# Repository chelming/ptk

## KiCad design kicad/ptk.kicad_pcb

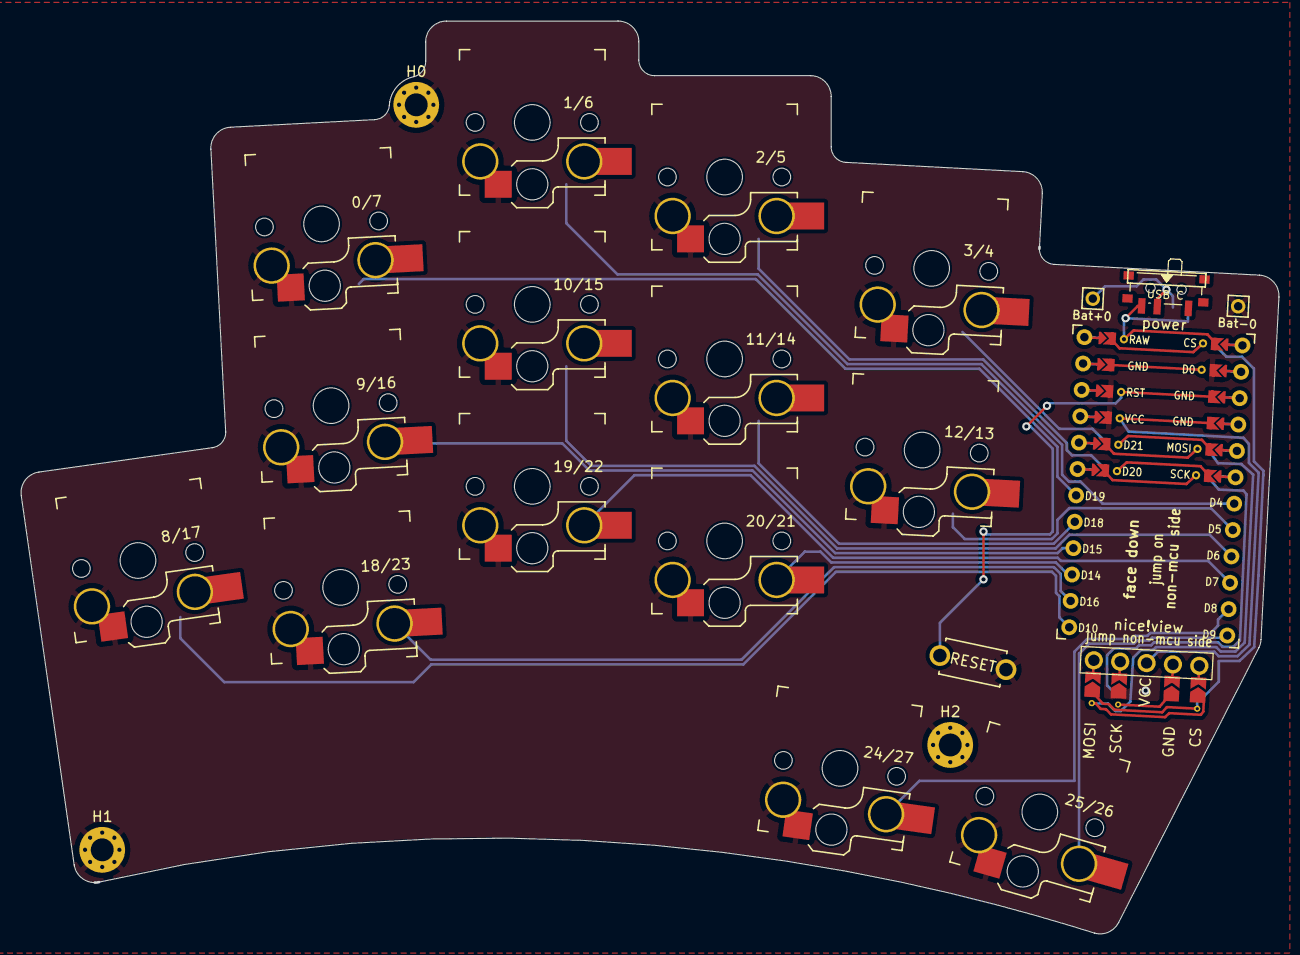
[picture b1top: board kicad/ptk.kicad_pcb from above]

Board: 2 copper layers, 121.0 x 87.8 mm, 23 parts (0 on the bottom side), 22 nets.

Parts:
0/7, 1/6, 2/5, 3/4, 8/17, 9/16, 10/15, 11/14, 12/13, 18/23, 19/22, 20/21, 24/27, 25/26: keyswitch; choc_v1_hotswap_reversible
Bat+0: MountingHole_Pad; 1pin_conn
Bat-0: MountingHole_Pad; 1pin_conn
H0, H1, H2: MountingHole_Pad; MountingHole_2.2mm_M2_Pad_Via
J0: nice!view; nice-view_reversible
MCU0: ProMicro-kbd; ProMicro_v3_nice_view_reversible
RSW0: SW_Push; ResetSW
SW_PWR0: SW_SPST; SW_SPDT_PCM12_REVERSIBLE

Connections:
+BATT: Bat+0.1, SW_PWR0.1 (A)
GND: 0/7.1, 1/6.1, 2/5.1, 3/4.1, 8/17.1, 9/16.1, 10/15.1, 11/14.1, 12/13.1, 18/23.1, 19/22.1, 20/21.1, 24/27.1, 25/26.1, Bat-0.1, H0.1, H1.1, H2.1, J0.4, MCU0.3 (GND), MCU0.4 (GND), MCU0.23 (GND), RSW0.1
VCC: J0.3, MCU0.21 (VCC)
cs: J0.5, MCU0.1 (TX)
mosi: J0.1, MCU0.5 (SDA)
raw: MCU0.24 (RAW), SW_PWR0.2 (B)
reset: MCU0.22 (RST), RSW0.2
s0: 0/7.2, MCU0.18 (F6)
s1: 1/6.2, MCU0.7 (D4)
s2: 2/5.2, MCU0.19 (F5)
s3: 3/4.2, MCU0.20 (F4)
s8: 8/17.2, MCU0.13 (B6)
s9: 9/16.2, MCU0.16 (B1)
s10: 10/15.2, MCU0.9 (D7)
s11: 11/14.2, MCU0.17 (F7)
s12: 12/13.2, MCU0.8 (C6)
s18: 18/23.2, MCU0.14 (B2)
s19: 19/22.2, MCU0.10 (E6)
s20: 20/21.2, MCU0.15 (B3)
s24: 24/27.2, MCU0.11 (B4)
s25: 25/26.2, MCU0.12 (B5)
sck: J0.2, MCU0.6 (SCL)

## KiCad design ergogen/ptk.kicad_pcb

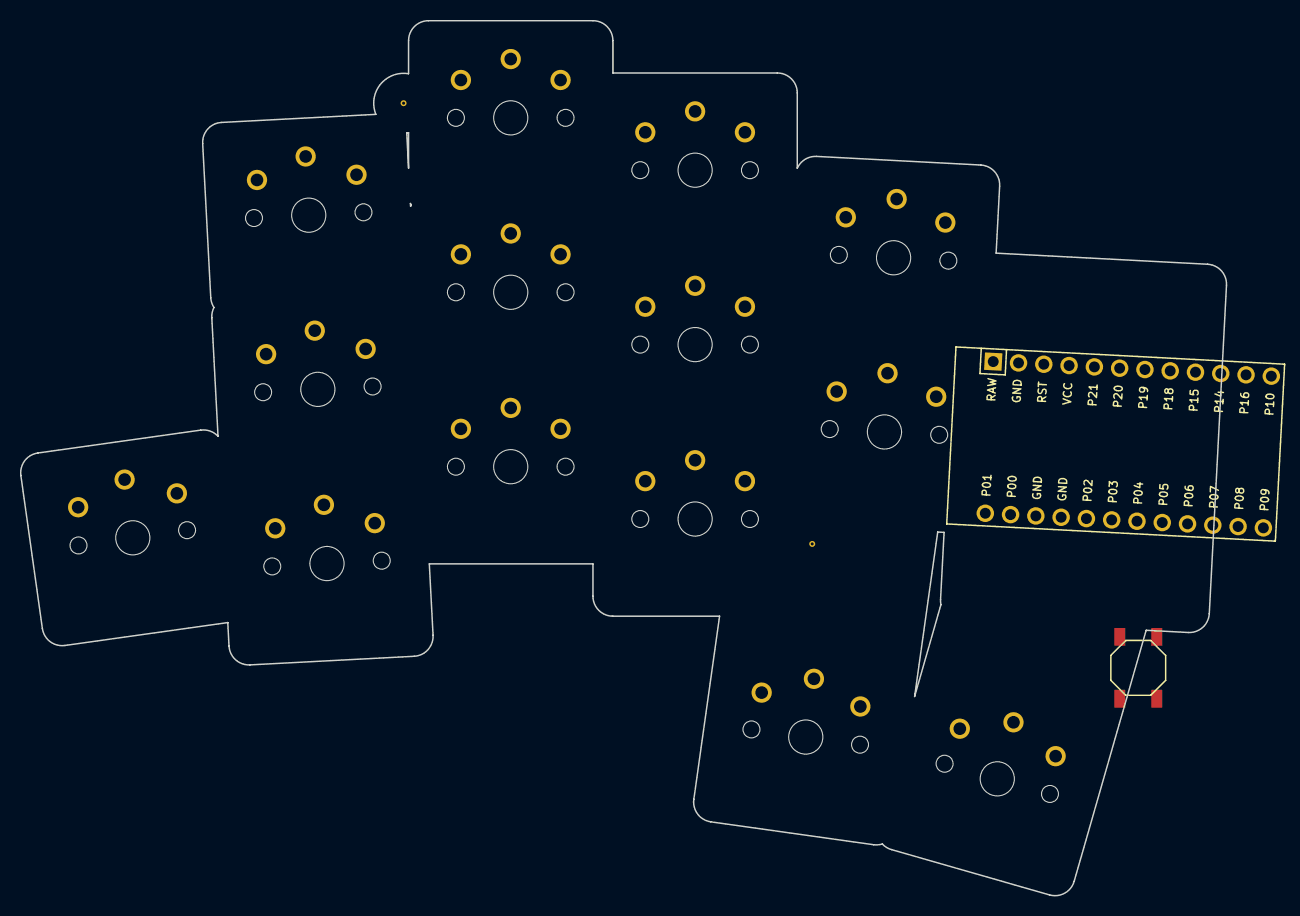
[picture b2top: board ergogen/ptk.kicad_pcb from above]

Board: 2 copper layers, 121.0 x 87.8 mm, 16 parts (0 on the bottom side), 16 nets, no tracks yet.

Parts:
B1: SW_TACT_ALPS_SKQGABE010
MCU1: ProMicro
S1, S2, S3, S4, S5, S6, S7, S8, S9, S10, S11, S12, S13, S14: PG1350

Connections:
GND: B1.2, MCU1.2, MCU1.15, MCU1.16, S1.1, S2.1, S3.1, S4.1, S5.1, S6.1, S7.1, S8.1, S9.1, S10.1, S11.1, S12.1, S13.1, S14.1
RST: B1.1, MCU1.3
matrix_index_bottom: MCU1.20, S8.2
matrix_index_home: MCU1.19, S9.2
matrix_index_top: MCU1.18, S10.2
matrix_inner_home: MCU1.22, S11.2
matrix_inner_top: MCU1.21, S12.2
matrix_middle_bottom: MCU1.12, S5.2
matrix_middle_home: MCU1.11, S6.2
matrix_middle_top: MCU1.10, S7.2
matrix_pinky_home: MCU1.6, S1.2
matrix_ring_bottom: MCU1.9, S2.2
matrix_ring_home: MCU1.8, S3.2
matrix_ring_top: MCU1.7, S4.2
thumb_reachy: MCU1.23, S14.2
thumb_tucky: MCU1.24, S13.2

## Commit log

2024-07-01 adding gitignore
2024-07-01 adjusting thumb
2024-07-02 wider thumb
2024-07-02 adding ergogen files
2024-07-03 adding kicad files. linking submodules
2024-07-09 updated schematic and footprints
2024-07-09 add'l routing
2024-07-10 added boxes around the keys on the schematic because I'm weird like that
2024-08-29 removing mounting hole
2024-08-29 adding the pinky back. I think
